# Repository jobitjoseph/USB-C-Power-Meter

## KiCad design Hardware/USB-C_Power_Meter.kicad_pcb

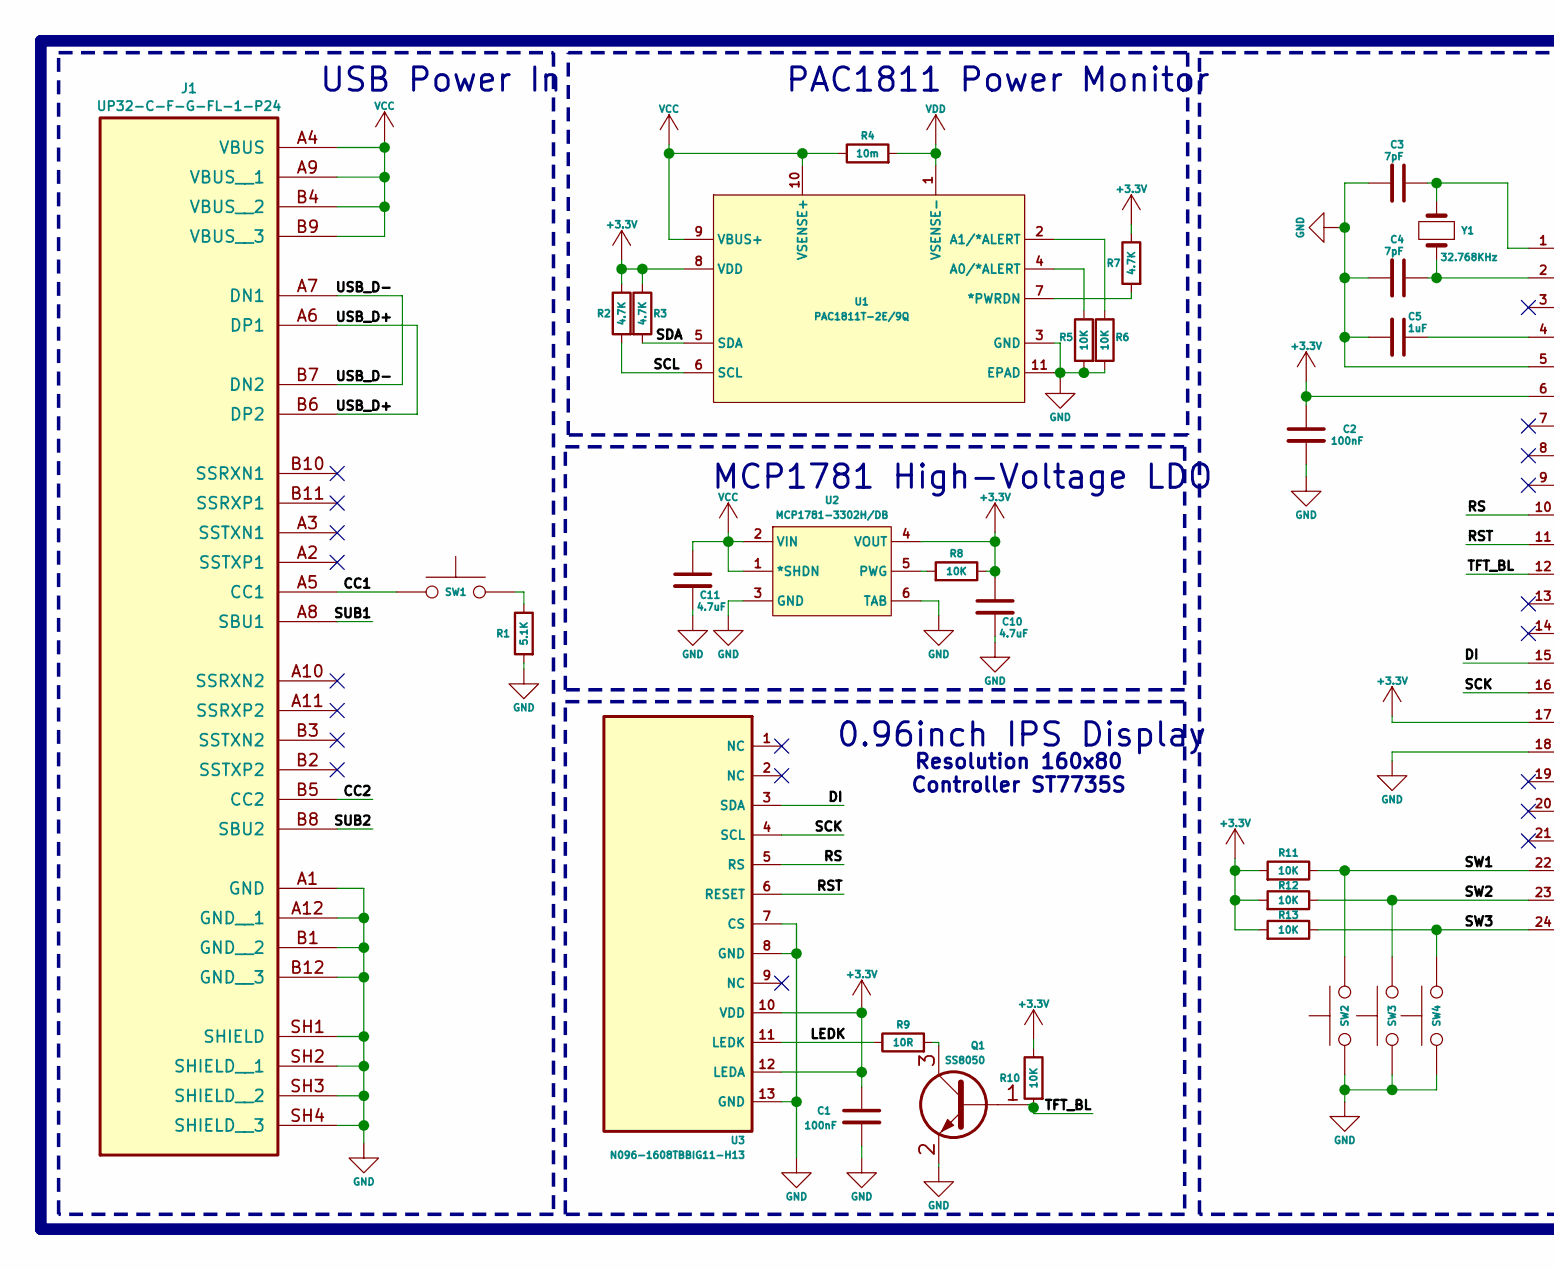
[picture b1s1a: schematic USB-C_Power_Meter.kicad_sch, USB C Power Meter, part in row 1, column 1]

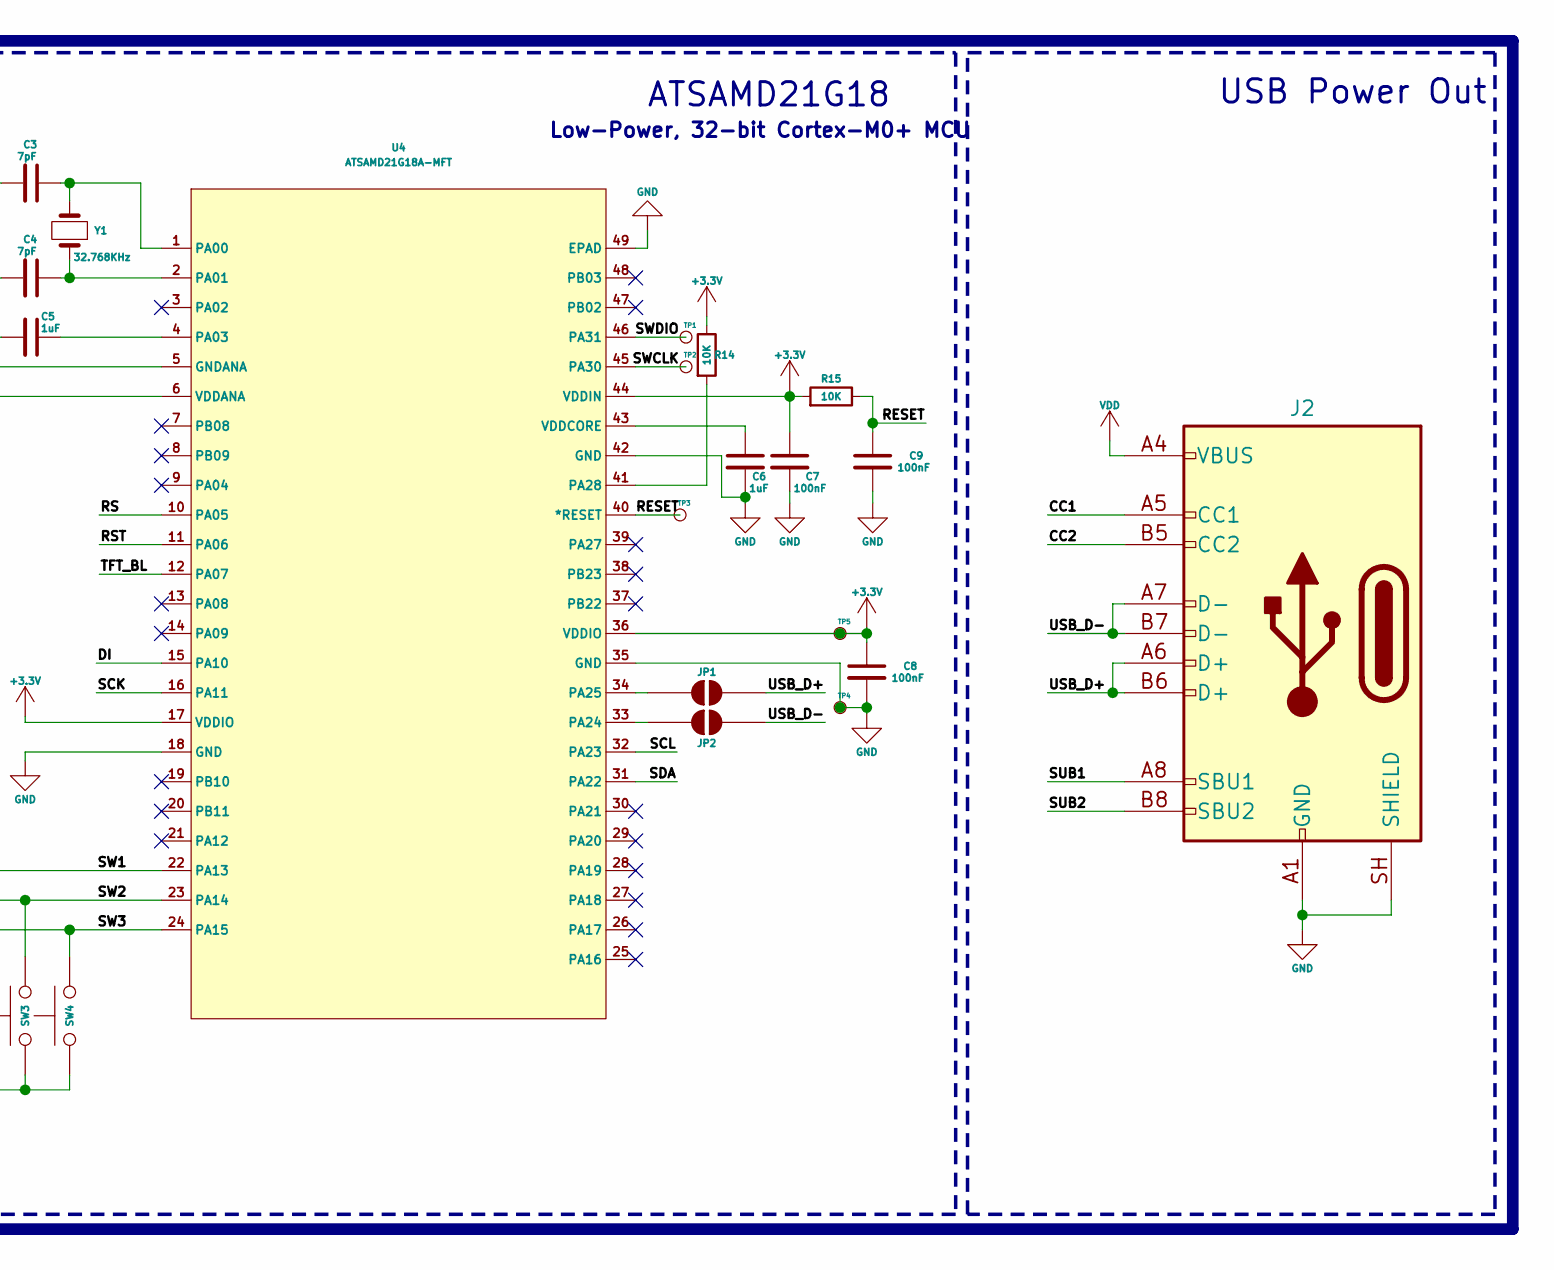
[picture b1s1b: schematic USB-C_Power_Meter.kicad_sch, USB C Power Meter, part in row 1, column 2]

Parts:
C1, C2, C7, C8, C9: 100nF; C_0402_1005Metric
C3, C4: 7pF; C_0402_1005Metric
C5, C6: 1uF; C_0402_1005Metric
C10, C11: 4.7uF; C_0603_1608Metric
J1: UP32-C-F-G-FL-1-P24; USB_C_Plug_Molex_105444; PARTREV 1.01; LCSC Part # C42453853
J2: USB_C_Receptacle_USB2.0_16P; USB_C_Receptacle_HRO_TYPE-C-31-M-12
JP1, JP2: SolderJumper_2_Open; SolderJumper-2_P1.3mm_Open_TrianglePad1.0x1.5mm
Q1: SS8050; SOT-23
R1: 5.1K; R_0402_1005Metric
R2, R3, R7: 4.7K; R_0402_1005Metric
R4: 10m; R_2512_6332Metric
R5, R6, R8, R10, R11, R12, R13, R14, R15: 10K; R_0402_1005Metric
R9: 10R; R_0603_1608Metric
SW1, SW2, SW3, SW4: Untitled
TP1, TP2, TP3, TP4, TP5: TestPoint_Small; TestPoint_Pad_D1.0mm
U1: PAC1811T-2E/9Q; VDFN10_9QX_MCH
U2: MCP1781-3302H/DB; SOT_223_5L_MCH
U3: N096-1608TBBIG11-H13; OLED-SMD_ST7735S; Manufacturer Part N096-1608TBBIG11-H13; LCSC Part Name 0.96寸 13PIN TFT显示模块
U4: ATSAMD21G18A-MFT; QFN48_7X7MC_MCH
Y1: 32.768KHz; Crystal_SMD_MicroCrystal_CM9V-T1A-2Pin_1.6x1.0mm_HandSolder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

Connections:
+3.3V: C1.1, C2.1, C7.1, C8.1, C10.1, R2.2, R3.2, R7.2, R8.2, R10.2, R11.1, R12.1, R13.1, R14.2, R15.1, TP5.1 (1_1), U1.8 (VDD), U2.4 (VOUT), U3.10 (VDD), U3.12 (LEDA), U4.6 (VDDANA), U4.17 (VDDIO), U4.36 (VDDIO), U4.44 (VDDIN)
/CC1: J1.A5 (CC1), J2.A5 (CC1), SW1.1
/CC2: J1.B5 (CC2), J2.B5 (CC2)
/DI: U3.3 (SDA), U4.15 (PA10)
/LEDK: R9.2, U3.11 (LEDK)
/RESET: C9.1, R15.2, TP3.1 (1_1), U4.40 (*RESET)
/RS: U3.5 (RS), U4.10 (PA05)
/RST: U3.6 (RESET), U4.11 (PA06)
/SCK: U3.4 (SCL), U4.16 (PA11)
/SCL: R2.1, U1.6 (SCL), U4.32 (PA23)
/SDA: R3.1, U1.5 (SDA), U4.31 (PA22)
/SUB1: J1.A8 (SBU1), J2.A8 (SBU1)
/SUB2: J1.B8 (SBU2), J2.B8 (SBU2)
/SW1: R11.2, SW2.2, U4.22 (PA13)
/SW2: R12.2, SW3.2, U4.23 (PA14)
/SW3: R13.2, SW4.1, U4.24 (PA15)
/SWCLK: TP2.1 (1_1), U4.45 (PA30)
/SWDIO: TP1.1 (1_1), U4.46 (PA31)
/TFT_BL: Q1.1 (B), R10.1, U4.12 (PA07)
/USB_D+: J1.A6 (DP1), J1.B6 (DP2), J2.A6 (D+), J2.B6 (D+), JP1.2 (B)
/USB_D-: J1.A7 (DN1), J1.B7 (DN2), J2.A7 (D-), J2.B7 (D-), JP2.2 (B)
GND: C1.2, C2.2, C3.2, C4.2, C5.2, C6.2, C7.2, C8.2, C9.2, C10.2, C11.2, J1.A1 (GND), J1.A12 (GND__1), J1.B1 (GND__2), J1.B12 (GND__3), J1.SH, J1.SH1 (SHIELD), J1.SH2 (SHIELD__1), J1.SH3 (SHIELD__2), J1.SH4 (SHIELD__3), J2.A1 (GND), J2.A12 (GND), J2.B1 (GND), J2.B12 (GND), J2.SH (SHIELD), Q1.2 (E), R1.1, R5.1, R6.1, SW2.1, SW3.1, SW4.2, TP4.1 (1_1), U1.3 (GND), U1.11 (EPAD), U2.3 (GND), U2.6 (TAB), U3.7 (CS), U3.8 (GND), U3.13 (GND), U4.5 (GNDANA), U4.18 (GND), U4.35 (GND), U4.42 (GND), U4.49 (EPAD)
unnamed: JP1.1 (A), U4.34 (PA25)
unnamed: JP2.1 (A), U4.33 (PA24)
unnamed: Q1.3 (C), R9.1
unnamed: R1.2, SW1.2
unnamed: R7.1, U1.7 (*PWRDN)
unnamed: R5.2, U1.4 (A0/*ALERT)
unnamed: R6.2, U1.2 (A1/*ALERT)
unnamed: R8.1, U2.5 (PWG)
unnamed: C3.1, U4.1 (PA00), Y1.2
unnamed: C4.1, U4.2 (PA01), Y1.1
unnamed: C5.1, U4.4 (PA03)
unnamed: R14.1, U4.41 (PA28)
unnamed: C6.1, U4.43 (VDDCORE)
VCC: C11.1, J1.A4 (VBUS), J1.A9 (VBUS__1), J1.B4 (VBUS__2), J1.B9 (VBUS__3), R4.2, U1.9 (VBUS+), U1.10 (VSENSE+), U2.1 (*SHDN), U2.2 (VIN)
VDD: J2.A4 (VBUS), J2.A9 (VBUS), J2.B4 (VBUS), J2.B9 (VBUS), R4.1, U1.1 (VSENSE-)

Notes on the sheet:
ATSAMD21G18
PAC1811 Power Monitor
Resolution 160x80 Controller ST7735S
Low-Power, 32-bit Cortex-M0+ MCU
USB Power In
MCP1781 High-Voltage LDO
0.96inch IPS Display
USB Power Out

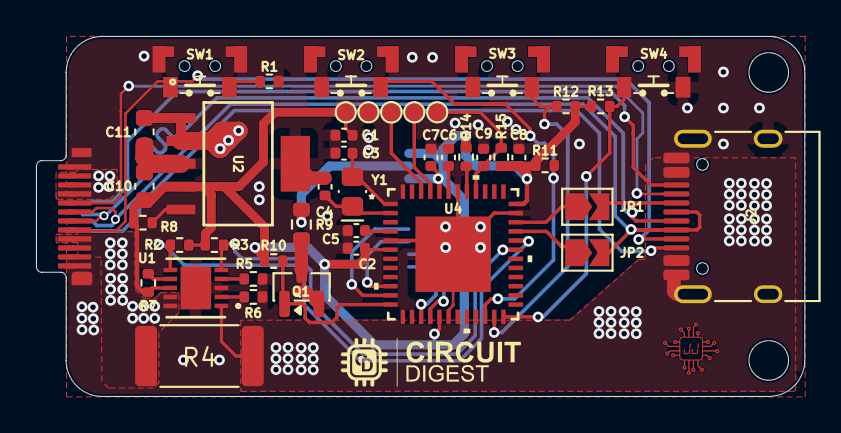
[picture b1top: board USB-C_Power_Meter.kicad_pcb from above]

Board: 4 copper layers, 42.7 x 20.0 mm, 45 parts (1 on the bottom side), 37 nets.

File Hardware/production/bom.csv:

Designator,Footprint,Quantity,Value,LCSC Part #
"C1, C2, C3, C4, C7, C8, C9",0402,7,100nF,
"C10, C11",0603,2,4.7uF,
"C5, C6",0402,2,1uF,
J1,USB_C_Plug_Molex_105444,1,UP32-C-F-G-FL-1-P24,C42453853
J2,USB_C_Receptacle_HRO_TYPE-C-31-M-12,1,USB_C_Receptacle_USB2.0_16P,
Q1,SOT-23,1,SS8050,
R1,0402,1,5.1K,
"R10, R11, R12, R13, R14, R15, R5, R6, R8",0402,9,10K,
"R2, R3, R7",0402,3,4.7K,
R4,2512,1,10m,
R9,0603,1,10R,
"SW1, SW2, SW3, SW4",Untitled,4,~,
"TP1, TP2, TP3, TP4, TP5",TestPoint_Pad_D1.0mm,5,TestPoint_Small,
U1,VDFN10_9QX_MCH,1,PAC1811T-2E/9Q,
U2,SOT_223_5L_MCH,1,MCP1781-3302H/DB,
U3,OLED-SMD_ST7735S,1,N096-1608TBBIG11-H13,
U4,QFN48_7X7MC_MCH,1,ATSAMD21G18A-MFT,
Y1,Crystal_SMD_MicroCrystal_CM9V-T1A-2Pin_1.6x1.0mm_HandSoldering,1,32.768KHz,

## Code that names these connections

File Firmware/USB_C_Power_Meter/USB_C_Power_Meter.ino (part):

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// not the hardware SPI pins). CS is tied to GND on the board, so it is
// passed to the display library as -1.
#define TFT_CS   -1     // tied to GND on the board
#define TFT_DC    A4    // RS / DC          (PA05)
#define TFT_RST   8     // RST              (PA06)
#define TFT_BL    9     // Backlight (PWM)  (PA07)
#define TFT_MOSI  1     // MOSI             (PA10)
#define TFT_SCK   0     // SCK              (PA11)

#define TFT_W 160
#define TFT_H 80
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
// Buttons — active LOW, with external 10k pull-ups on the board, so the
// internal pull-ups are left disabled.
// PA13/PA14/PA15 are not usable via Arduino's pin API on this board
// profile: variant.h caps PINS_COUNT at 26, so even though PA13 has an
// entry further down in variant.cpp's g_APinDescription[] table,
// pinMode(), digitalRead() and attachInterrupt() only recognise pins
// 0..25. These three are therefore driven with direct SAMD21 PORT
// register access — see gpioInput() and gpioActiveLow() below.
#define SW_NEXT_BIT  13   // PA13
#define SW_ROT_BIT   14   // PA14 — tap = flip display 180°, hold 1.5s = reset
#define SW_PREV_BIT  15   // PA15

// PAC1811T-2E power monitor — I2C on the board's default SDA/SCL
#define PAC1811_I2C_ADDR   0x40
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    lastChangeMs(0), pressStartMs(0), holdFired(false) {}
};

// PA13/PA14/PA15 are not on this board profile's pin table (variant.h
// caps PINS_COUNT at 26), so they are configured and read through the
// SAMD21 PORT registers instead of pinMode()/digitalRead().
static inline void gpioInput(uint8_t bit) {
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}

void begin() {
  pinMode(TFT_BL, OUTPUT);
  digitalWrite(TFT_BL, HIGH);

  // INITR_MINI160x80 is the standard init sequence for 160x80 ST7735 IPS
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// ============================================================
//  BUTTONS
// ============================================================
// PA13 pages forward, PA15 pages back. PA14 flips the display 180° on a
// tap and resets the session on a 1.5s hold.
const unsigned long DEBOUNCE_MS = 25;
const unsigned long HOLD_MS = 1500;
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    needFullRedraw = true;
  }

  // PA14: tap = flip 180°, hold 1.5s = reset
  bool relRot;
  bool pressedRot = pollEdge(btnRot, relRot);
  if (pressedRot) {
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

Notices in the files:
Firmware/USB_C_Power_Meter/USB_C_Power_Meter.ino:
Copyright © Jobit Joseph
Copyright © Semicon Media Pvt Ltd
Copyright © Circuitdigest.com
